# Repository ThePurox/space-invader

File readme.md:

The space-invader was conceptualized [kilipan](https://github.com/kilipan). I liked the idea so much that I realized the board.

A single board can be used as a macropad, but it really shines, when two boards are used together. Then it acts like a split [humming bird keyboard](https://github.com/PJE66/hummingbird).
The board uses [XIAO-nRF52840](https://wiki.seeedstudio.com/XIAO_BLE/) controllers.

# Buildguide

Before we start, I need to clarify some nomenclature:
I'll refer to side of the PCB with the silkscreen credits as the bottom side.

Solder the diodes to the top side of the PCB. Be careful with the orientation of the diodes! The closed side of the silkscreen on the PCB marks the cathode (the side of the diode with the line on it).
Next solder in the XIAO face down, i.e. such that its components are visible from the bottom side of the PCB.

If you want to use the on/off switch for the battery solder it onto the bottom side of the PCB. Then solder the positive side of the battery to the pad labeled `BAT+` on the front side of the PCB. Next solder a cable from the pad labeled `MCU+` on the PCB to the pad labeled `BAT+` on the XIAO. Finally solder the negative side of the battery directly to the XIAO.

In case you don't want to use the on/off switch solder the battery directly to the battery pads on the XIAO.

When installing the switches you have a choice. As the PCB is reversible, you can install the switches from both sides.
It you want to use a plate, you have three options, there is one [universal plate](plate_reversible.stl), which can be used with both PCB orientations, but you will have cutouts on the top of the plate.
The [plate_top_holes.stl](plate_top_holes.stl) is designed to be used with the switches installed from the top. And [plate_bottom_holes.stl](plate_bottom_holes.stl) is designed to be used with the switches installed from the bottom.
Install the switches through the plate into the PCB and solder them to the PCB.

# Flashing firmware
The firmware for this board can be found at [https://github.com/ThePurox/space-invader-zmk/](https://github.com/ThePurox/space-invader-zmk/).

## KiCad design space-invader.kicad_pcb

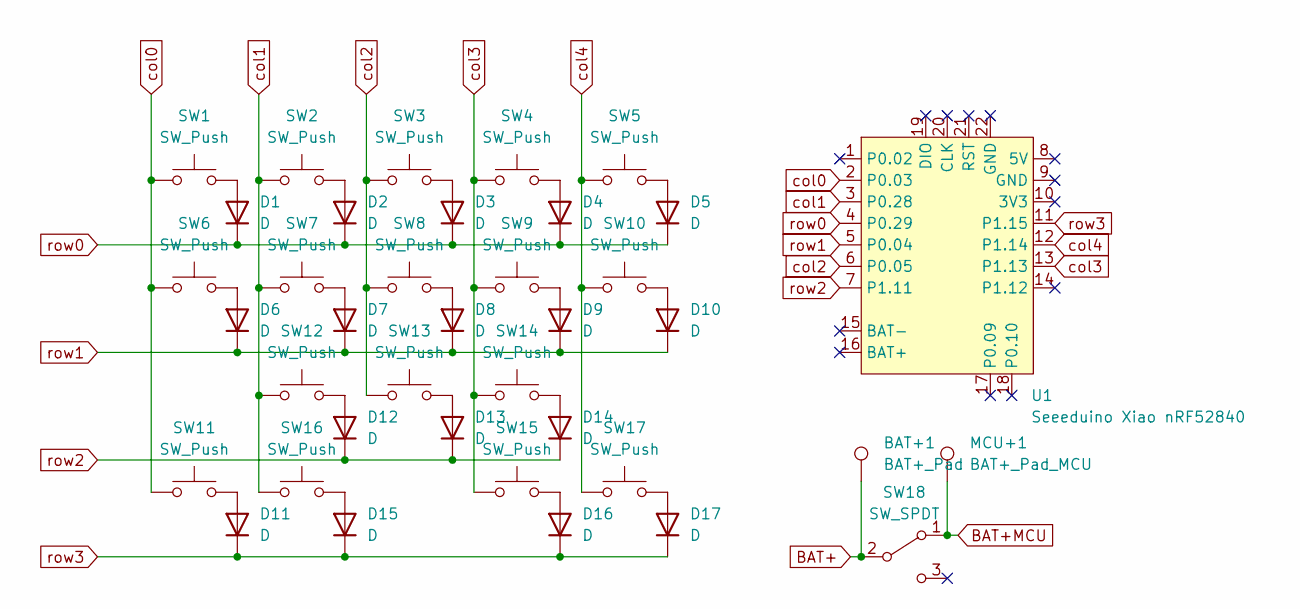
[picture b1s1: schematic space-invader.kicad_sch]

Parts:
BAT+1: BAT+_Pad; TestPoint_Pad_1.5x1.5mm
D1, D2, D3, D4, D5, D6, D7, D8, D9, D10, D11, D12, D13, D14, D15, D16, D17: D; D_0805_2012Metric_Pad1.15x1.40mm_HandSolder
MCU+1: BAT+_Pad_MCU; TestPoint_Pad_1.5x1.5mm
SW1, SW2, SW3, SW4, SW5, SW6, SW7, SW8, SW9, SW10, SW11, SW12, SW13, SW14, SW15, SW16, SW17: SW_Push; SW_MX_Reversible_1u
SW18: SW_SPDT; SW_MSK12C02-HB
U1: Seeeduino Xiao nRF52840; Xiao_nRF52840_AC_Reflow_invert

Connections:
BAT+: BAT+1.1, SW18.2 (B); also elsewhere on the board
BAT+MCU: MCU+1.1, SW18.1 (A); also elsewhere on the board
unnamed: D1.2 (A), SW1.2
unnamed: D2.2 (A), SW2.2
unnamed: D3.2 (A), SW3.2
unnamed: D4.2 (A), SW4.2
unnamed: D5.2 (A), SW5.2
unnamed: D6.2 (A), SW6.2
unnamed: D7.2 (A), SW7.2
unnamed: D8.2 (A), SW8.2
unnamed: D9.2 (A), SW9.2
unnamed: D10.2 (A), SW10.2
unnamed: D11.2 (A), SW11.2
unnamed: D12.2 (A), SW12.2
unnamed: D13.2 (A), SW13.2
unnamed: D14.2 (A), SW14.2
unnamed: D15.2 (A), SW16.2
unnamed: D16.2 (A), SW15.2
unnamed: D17.2 (A), SW17.2
col0: SW1.1, SW6.1, SW11.1, U1.2 (P0.03)
col1: SW2.1, SW7.1, SW12.1, SW16.1, U1.3 (P0.28)
col2: SW3.1, SW8.1, SW13.1, U1.6 (P0.05)
col3: SW4.1, SW9.1, SW14.1, SW15.1, U1.13 (P1.13)
col4: SW5.1, SW10.1, SW17.1, U1.12 (P1.14)
row0: D1.1 (K), D2.1 (K), D3.1 (K), D4.1 (K), D5.1 (K), U1.4 (P0.29)
row1: D6.1 (K), D7.1 (K), D8.1 (K), D9.1 (K), D10.1 (K), U1.5 (P0.04)
row2: D12.1 (K), D13.1 (K), D14.1 (K), U1.7 (P1.11)
row3: D11.1 (K), D15.1 (K), D16.1 (K), D17.1 (K), U1.11 (P1.15)

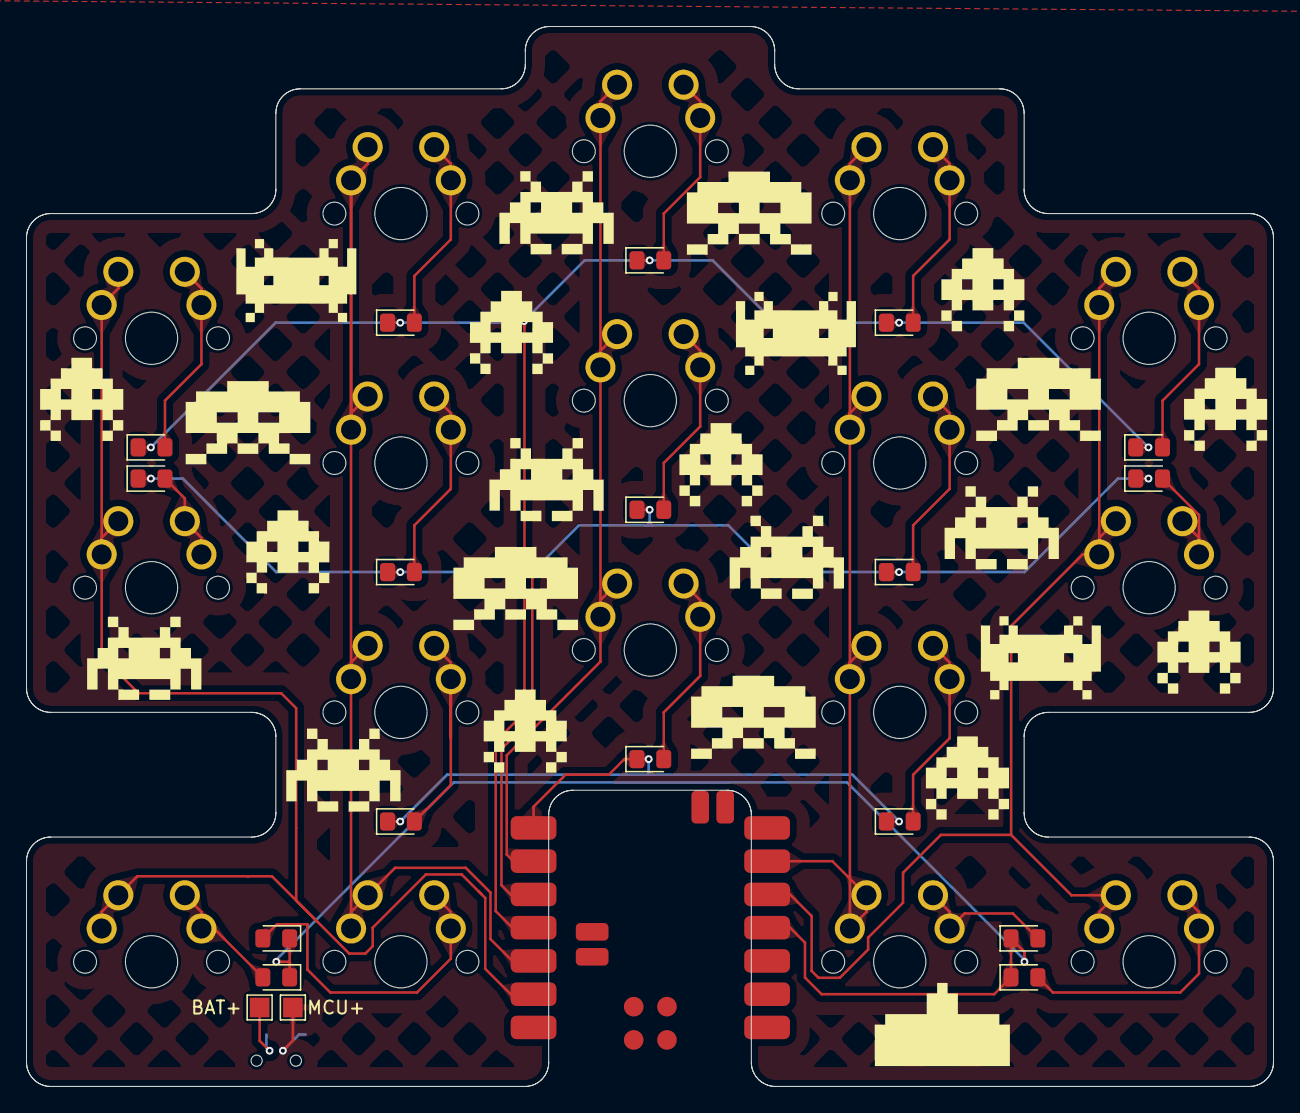
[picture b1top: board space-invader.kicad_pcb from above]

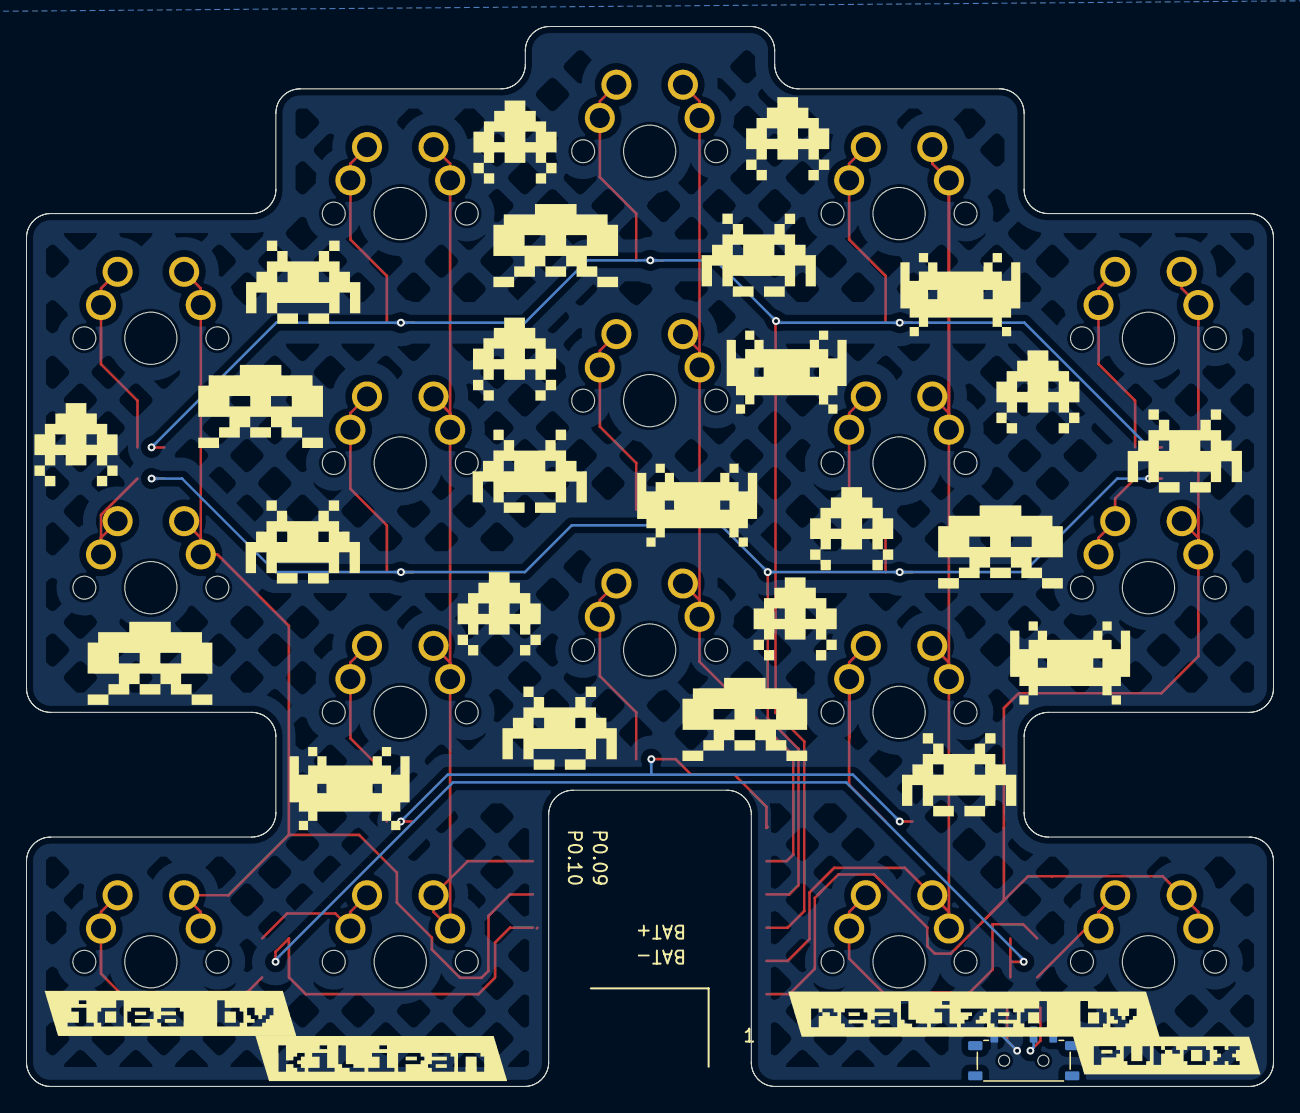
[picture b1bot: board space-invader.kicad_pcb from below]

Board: 2 copper layers, 95.3 x 81.0 mm, 42 parts (6 on the bottom side), 28 nets.

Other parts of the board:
BAT+: BAT+_Pad; TestPoint_Pad_1.5x1.5mm
MCU+: BAT+_Pad_MCU; TestPoint_Pad_1.5x1.5mm
kibuzzard-67AF24A7: G***; kibuzzard-67AF24A7
kibuzzard-67AF24D7: G***; kibuzzard-67AF24D7
kibuzzard-67AF254E: G***; kibuzzard-67AF254E
kibuzzard-67AF2568: G***; kibuzzard-67AF2568

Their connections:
BAT+: BAT+.1; also elsewhere on the board
BAT+MCU: MCU+.1; also elsewhere on the board

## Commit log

2025-01-28 first bare version
2025-01-29 updated pictures
2025-01-29 there be graphics
2025-02-14 flipped XIAO upside down
2025-02-15 added readme and plate
2025-02-16 added on-off switch
2025-02-26 added working reversible switch-plate
2025-02-26 added top and bottom switch-plates
2025-02-26 increased z height for xiao
2025-02-26 added cutout for battery cables
2025-03-15 buildguide
2025-03-15 fixed picture
